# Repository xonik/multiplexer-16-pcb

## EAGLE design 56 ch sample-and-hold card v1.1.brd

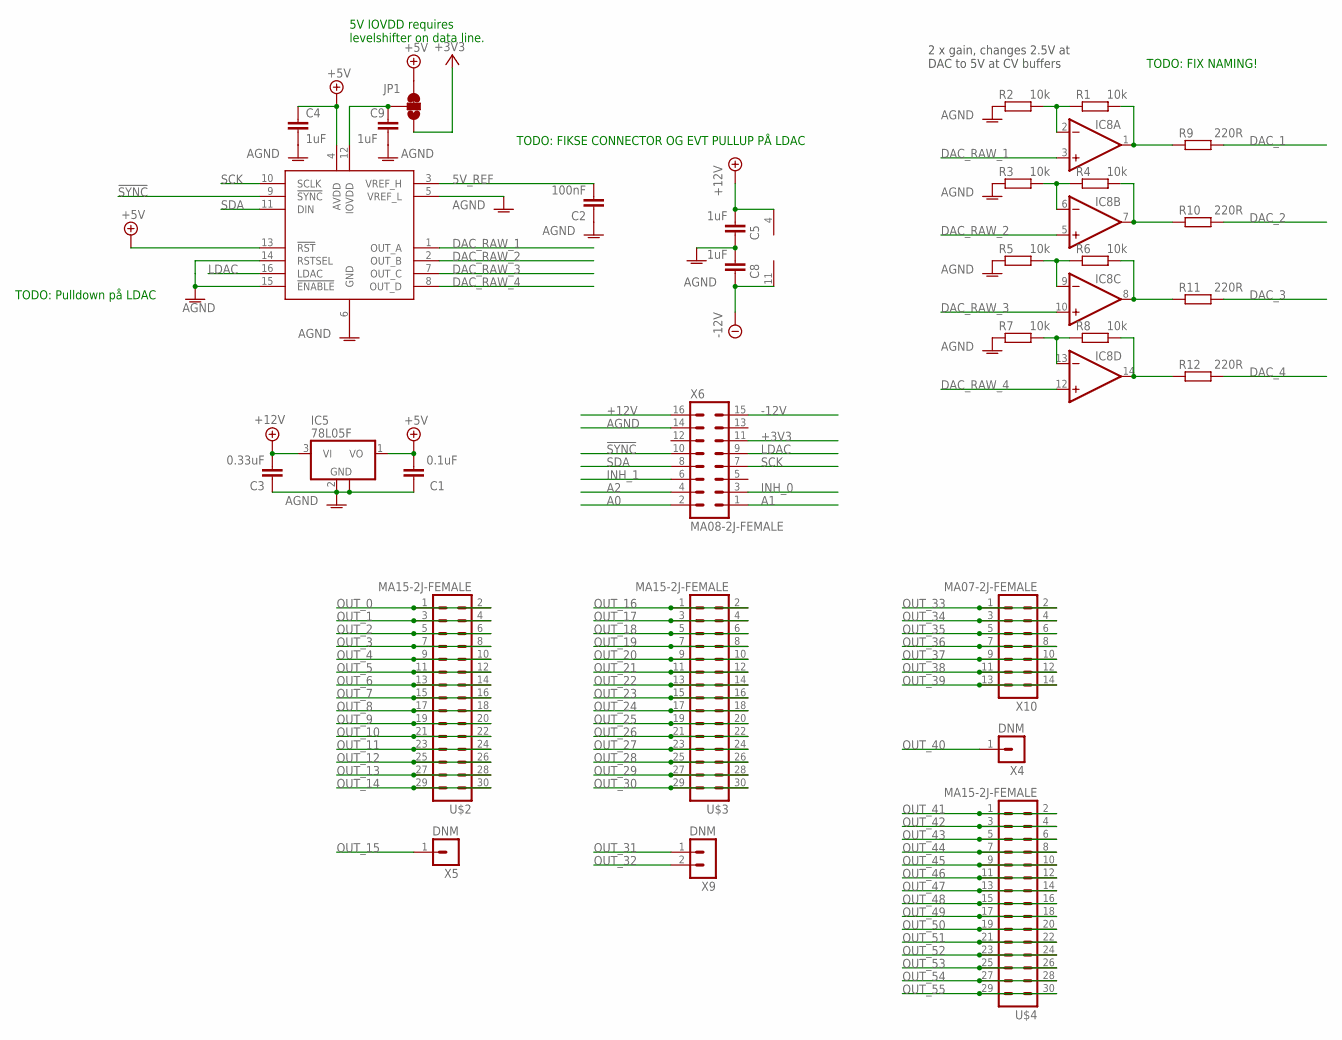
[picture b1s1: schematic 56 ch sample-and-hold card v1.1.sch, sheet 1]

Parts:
C1: 0.1uF; C0603
C2: 100nF; C0603
C3: 0.33uF; C0603
C4, C5, C8, C9: 1uF; C0402-J
IC2: DAC8565F; DIL16-FM-CON
IC5: 78L05F; SOT89
IC8: TL074JT; TSSOP14J
JP1: JUMPER-SMT_3_1-NC_TRACE_NO-SILK_DNM; SMT-JUMPER_3_1-NC_TRACE_NO-SILK
R1, R2, R3, R4, R5, R6, R7, R8: 10k; R0603
R9, R10, R11, R12: 220R; R0603
U$2, U$3, U$4: MA15-2J-FEMALE; MA15-2J
X4, X5: DNM; MA01N-1J
X6: MA08-2J-FEMALE; MA08-2J
X9: DNM; MA02N-1J
X10: MA07-2J-FEMALE; MA07-2J

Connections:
5V_REF: C2.2, IC2.3 (VREF_H)
!SYNC: IC2.9 (!SYNC), X6.10
+3V3: JP1.1, X6.11
+5V: C1.2, C4.1, IC2.4 (AVDD), IC2.13 (!RST), IC5.1 (VO), JP1.3; also elsewhere on the board
+12V: C3.2, C5.1, IC5.3 (VI), IC8.4 (V+), X6.16; also elsewhere on the board
-12V: C8.2, IC8.11 (V-), X6.15; also elsewhere on the board
A0: X6.2; also elsewhere on the board
A1: X6.1; also elsewhere on the board
A2: X6.4; also elsewhere on the board
AGND: C1.1, C2.1, C3.1, C4.2, C5.2, C8.1, C9.2, IC2.5 (VREF_L), IC2.6 (GND), IC2.14 (RSTSEL), IC2.15 (!ENABLE), IC5.2 (GND), IC5.2@1 (GND), R2.1, R3.1, R5.1, R7.1, X6.14; also elsewhere on the board
DAC_1: R9.2; also elsewhere on the board
DAC_2: R10.2; also elsewhere on the board
DAC_3: R11.2; also elsewhere on the board
DAC_4: R12.2; also elsewhere on the board
DAC_BUF_1: IC8.1 (OUT), R1.2, R9.1
DAC_BUF_2: IC8.7 (OUT), R4.2, R10.1
DAC_BUF_3: IC8.8 (OUT), R6.2, R11.1
DAC_BUF_4: IC8.14 (OUT), R8.2, R12.1
DAC_RAW_1: IC2.1 (OUT_A), IC8.3 (+IN)
DAC_RAW_2: IC2.2 (OUT_B), IC8.5 (+IN)
DAC_RAW_3: IC2.7 (OUT_C), IC8.10 (+IN)
DAC_RAW_4: IC2.8 (OUT_D), IC8.12 (+IN)
INH_0: X6.3; also elsewhere on the board
INH_1: X6.6; also elsewhere on the board
LDAC: IC2.16 (LDAC), X6.9
unnamed: C9.1, IC2.12 (IOVDD), JP1.2
unnamed: IC8.2 (-IN), R1.1, R2.2
unnamed: IC8.6 (-IN), R3.2, R4.1
unnamed: IC8.9 (-IN), R5.2, R6.1
unnamed: IC8.13 (-IN), R7.2, R8.1
OUT_0: U$2.1, U$2.2; also elsewhere on the board
OUT_1: U$2.3, U$2.4; also elsewhere on the board
OUT_2: U$2.5, U$2.6; also elsewhere on the board
OUT_3: U$2.7, U$2.8; also elsewhere on the board
OUT_4: U$2.9, U$2.10; also elsewhere on the board
OUT_5: U$2.11, U$2.12; also elsewhere on the board
OUT_6: U$2.13, U$2.14; also elsewhere on the board
OUT_7: U$2.15, U$2.16; also elsewhere on the board
OUT_8: U$2.17, U$2.18; also elsewhere on the board
OUT_9: U$2.19, U$2.20; also elsewhere on the board
OUT_10: U$2.21, U$2.22; also elsewhere on the board
OUT_11: U$2.23, U$2.24; also elsewhere on the board
OUT_12: U$2.25, U$2.26; also elsewhere on the board
OUT_13: U$2.27, U$2.28; also elsewhere on the board
OUT_14: U$2.29, U$2.30; also elsewhere on the board
OUT_15: X5.1; also elsewhere on the board
OUT_16: U$3.1, U$3.2; also elsewhere on the board
OUT_17: U$3.3, U$3.4; also elsewhere on the board
OUT_18: U$3.5, U$3.6; also elsewhere on the board
OUT_19: U$3.7, U$3.8; also elsewhere on the board
OUT_20: U$3.9, U$3.10; also elsewhere on the board
OUT_21: U$3.11, U$3.12; also elsewhere on the board
OUT_22: U$3.13, U$3.14; also elsewhere on the board
OUT_23: U$3.15, U$3.16; also elsewhere on the board
OUT_24: U$3.17, U$3.18; also elsewhere on the board
OUT_25: U$3.19, U$3.20; also elsewhere on the board
OUT_26: U$3.21, U$3.22; also elsewhere on the board
OUT_27: U$3.23, U$3.24; also elsewhere on the board
OUT_28: U$3.25, U$3.26; also elsewhere on the board
OUT_29: U$3.27, U$3.28; also elsewhere on the board
OUT_30: U$3.29, U$3.30; also elsewhere on the board
OUT_31: X9.1; also elsewhere on the board
OUT_32: X9.2; also elsewhere on the board
OUT_33: X10.1, X10.2; also elsewhere on the board
OUT_34: X10.3, X10.4; also elsewhere on the board
OUT_35: X10.5, X10.6; also elsewhere on the board
OUT_36: X10.7, X10.8; also elsewhere on the board
OUT_37: X10.9, X10.10; also elsewhere on the board
OUT_38: X10.11, X10.12; also elsewhere on the board
OUT_39: X10.13, X10.14; also elsewhere on the board
OUT_40: X4.1; also elsewhere on the board
OUT_41: U$4.1, U$4.2; also elsewhere on the board
OUT_42: U$4.3, U$4.4; also elsewhere on the board
OUT_43: U$4.5, U$4.6; also elsewhere on the board
OUT_44: U$4.7, U$4.8; also elsewhere on the board
OUT_45: U$4.9, U$4.10; also elsewhere on the board
OUT_46: U$4.11, U$4.12; also elsewhere on the board
OUT_47: U$4.13, U$4.14; also elsewhere on the board
OUT_48: U$4.15, U$4.16; also elsewhere on the board
OUT_49: U$4.17, U$4.18; also elsewhere on the board
OUT_50: U$4.19, U$4.20; also elsewhere on the board
OUT_51: U$4.21, U$4.22; also elsewhere on the board
OUT_52: U$4.23, U$4.24; also elsewhere on the board
OUT_53: U$4.25, U$4.26; also elsewhere on the board
OUT_54: U$4.27, U$4.28; also elsewhere on the board
OUT_55: U$4.29, U$4.30; also elsewhere on the board
SCK: IC2.10 (SCLK), X6.7
SDA: IC2.11 (DIN), X6.8

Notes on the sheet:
5V IOVDD requires levelshifter on data line.
TODO: FIKSE CONNECTOR OG EVT PULLUP PÅ LDAC
TODO: Pulldown på LDAC
TODO: FIX NAMING!
2 x gain, changes 2.5V at DAC to 5V at CV buffers

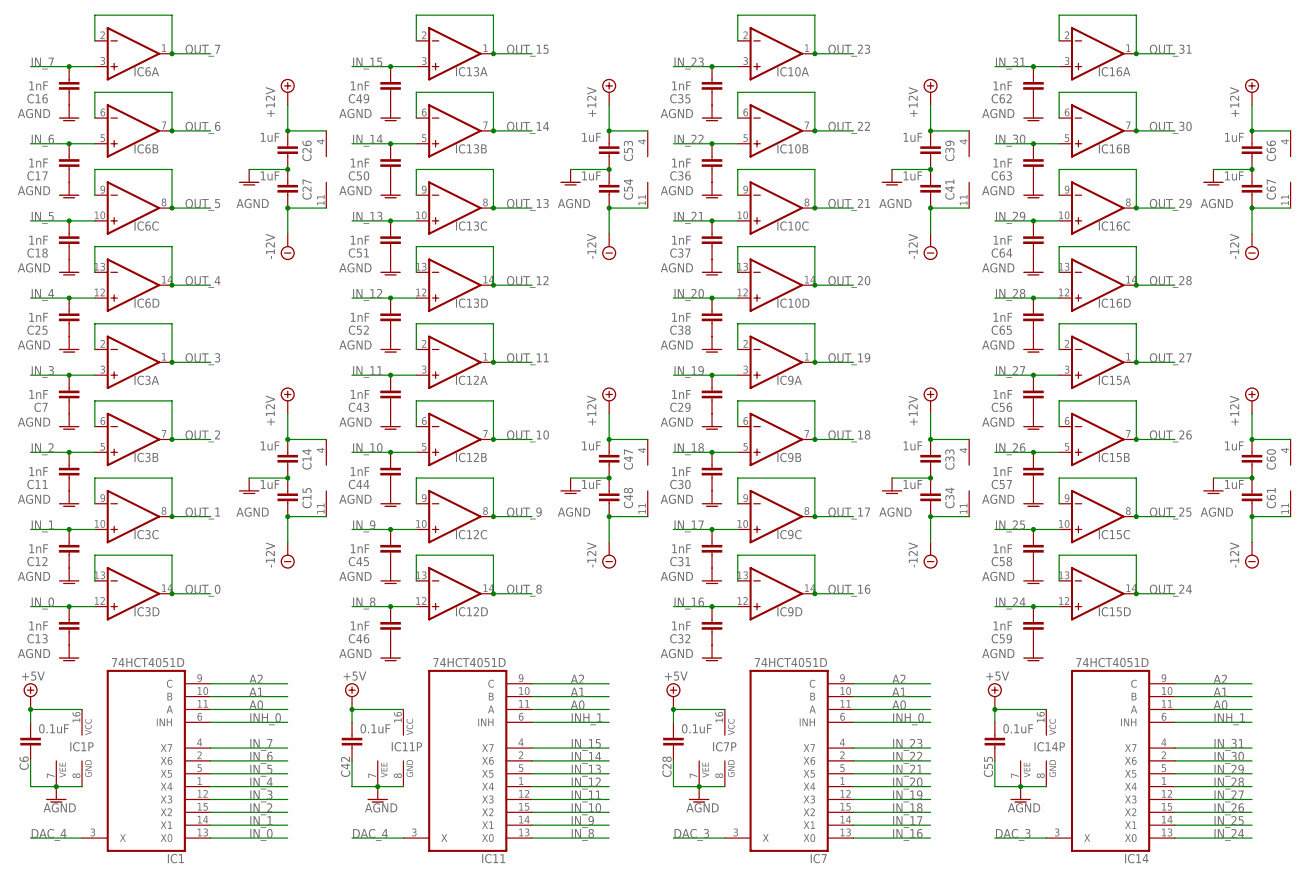
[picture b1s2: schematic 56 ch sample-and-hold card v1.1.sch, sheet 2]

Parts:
C6, C28, C42, C55: 0.1uF; C0402-J
C7, C11, C12, C13, C16, C17, C18, C25, C29, C30, C31, C32, C35, C36, C37, C38, C43, C44, C45, C46, C49, C50, C51, C52, C56, C57, C58, C59, C62, C63, C64, C65: 1nF; C0603-J
C14, C15, C26, C27, C33, C34, C39, C41, C47, C48, C53, C54, C60, C61, C66, C67: 1uF; C0402-J
IC1, IC7, IC11, IC14: 74HCT4051D; SO16
IC3, IC6, IC9, IC10, IC12, IC13, IC15, IC16: TL074JT; TSSOP14J

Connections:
+5V: C6.2, C28.2, C42.2, C55.2, IC1.16 (VCC), IC7.16 (VCC), IC11.16 (VCC), IC14.16 (VCC); also elsewhere on the board
+12V: C14.1, C26.1, C33.1, C39.1, C47.1, C53.1, C60.1, C66.1, IC3.4 (V+), IC6.4 (V+), IC9.4 (V+), IC10.4 (V+), IC12.4 (V+), IC13.4 (V+), IC15.4 (V+), IC16.4 (V+); also elsewhere on the board
-12V: C15.2, C27.2, C34.2, C41.2, C48.2, C54.2, C61.2, C67.2, IC3.11 (V-), IC6.11 (V-), IC9.11 (V-), IC10.11 (V-), IC12.11 (V-), IC13.11 (V-), IC15.11 (V-), IC16.11 (V-); also elsewhere on the board
A0: IC1.11 (A), IC7.11 (A), IC11.11 (A), IC14.11 (A); also elsewhere on the board
A1: IC1.10 (B), IC7.10 (B), IC11.10 (B), IC14.10 (B); also elsewhere on the board
A2: IC1.9 (C), IC7.9 (C), IC11.9 (C), IC14.9 (C); also elsewhere on the board
AGND: C6.1, C7.1, C11.1, C12.1, C13.1, C14.2, C15.1, C16.1, C17.1, C18.1, C25.1, C26.2, C27.1, C28.1, C29.1, C30.1, C31.1, C32.1, C33.2, C34.1, C35.1, C36.1, C37.1, C38.1, C39.2, C41.1, C42.1, C43.1, C44.1, C45.1, C46.1, C47.2, C48.1, C49.1, C50.1, C51.1, C52.1, C53.2, C54.1, C55.1, C56.1, C57.1, C58.1, C59.1, C60.2, C61.1, C62.1, C63.1, C64.1, C65.1, C66.2, C67.1, IC1.7 (VEE), IC1.8 (GND), IC7.7 (VEE), IC7.8 (GND), IC11.7 (VEE), IC11.8 (GND), IC14.7 (VEE), IC14.8 (GND); also elsewhere on the board
DAC_3: IC7.3 (X), IC14.3 (X); also elsewhere on the board
DAC_4: IC1.3 (X), IC11.3 (X); also elsewhere on the board
INH_0: IC1.6 (INH), IC7.6 (INH); also elsewhere on the board
INH_1: IC11.6 (INH), IC14.6 (INH); also elsewhere on the board
IN_0: C13.2, IC1.13 (X0), IC3.12 (+IN)
IN_1: C12.2, IC1.14 (X1), IC3.10 (+IN)
IN_2: C11.2, IC1.15 (X2), IC3.5 (+IN)
IN_3: C7.2, IC1.12 (X3), IC3.3 (+IN)
IN_4: C25.2, IC1.1 (X4), IC6.12 (+IN)
IN_5: C18.2, IC1.5 (X5), IC6.10 (+IN)
IN_6: C17.2, IC1.2 (X6), IC6.5 (+IN)
IN_7: C16.2, IC1.4 (X7), IC6.3 (+IN)
IN_8: C46.2, IC11.13 (X0), IC12.12 (+IN)
IN_9: C45.2, IC11.14 (X1), IC12.10 (+IN)
IN_10: C44.2, IC11.15 (X2), IC12.5 (+IN)
IN_11: C43.2, IC11.12 (X3), IC12.3 (+IN)
IN_12: C52.2, IC11.1 (X4), IC13.12 (+IN)
IN_13: C51.2, IC11.5 (X5), IC13.10 (+IN)
IN_14: C50.2, IC11.2 (X6), IC13.5 (+IN)
IN_15: C49.2, IC11.4 (X7), IC13.3 (+IN)
IN_16: C32.2, IC7.13 (X0), IC9.12 (+IN)
IN_17: C31.2, IC7.14 (X1), IC9.10 (+IN)
IN_18: C30.2, IC7.15 (X2), IC9.5 (+IN)
IN_19: C29.2, IC7.12 (X3), IC9.3 (+IN)
IN_20: C38.2, IC7.1 (X4), IC10.12 (+IN)
IN_21: C37.2, IC7.5 (X5), IC10.10 (+IN)
IN_22: C36.2, IC7.2 (X6), IC10.5 (+IN)
IN_23: C35.2, IC7.4 (X7), IC10.3 (+IN)
IN_24: C59.2, IC14.13 (X0), IC15.12 (+IN)
IN_25: C58.2, IC14.14 (X1), IC15.10 (+IN)
IN_26: C57.2, IC14.15 (X2), IC15.5 (+IN)
IN_27: C56.2, IC14.12 (X3), IC15.3 (+IN)
IN_28: C65.2, IC14.1 (X4), IC16.12 (+IN)
IN_29: C64.2, IC14.5 (X5), IC16.10 (+IN)
IN_30: C63.2, IC14.2 (X6), IC16.5 (+IN)
IN_31: C62.2, IC14.4 (X7), IC16.3 (+IN)
OUT_0: IC3.13 (-IN), IC3.14 (OUT); also elsewhere on the board
OUT_1: IC3.8 (OUT), IC3.9 (-IN); also elsewhere on the board
OUT_2: IC3.6 (-IN), IC3.7 (OUT); also elsewhere on the board
OUT_3: IC3.1 (OUT), IC3.2 (-IN); also elsewhere on the board
OUT_4: IC6.13 (-IN), IC6.14 (OUT); also elsewhere on the board
OUT_5: IC6.8 (OUT), IC6.9 (-IN); also elsewhere on the board
OUT_6: IC6.6 (-IN), IC6.7 (OUT); also elsewhere on the board
OUT_7: IC6.1 (OUT), IC6.2 (-IN); also elsewhere on the board
OUT_8: IC12.13 (-IN), IC12.14 (OUT); also elsewhere on the board
OUT_9: IC12.8 (OUT), IC12.9 (-IN); also elsewhere on the board
OUT_10: IC12.6 (-IN), IC12.7 (OUT); also elsewhere on the board
OUT_11: IC12.1 (OUT), IC12.2 (-IN); also elsewhere on the board
OUT_12: IC13.13 (-IN), IC13.14 (OUT); also elsewhere on the board
OUT_13: IC13.8 (OUT), IC13.9 (-IN); also elsewhere on the board
OUT_14: IC13.6 (-IN), IC13.7 (OUT); also elsewhere on the board
OUT_15: IC13.1 (OUT), IC13.2 (-IN); also elsewhere on the board
OUT_16: IC9.13 (-IN), IC9.14 (OUT); also elsewhere on the board
OUT_17: IC9.8 (OUT), IC9.9 (-IN); also elsewhere on the board
OUT_18: IC9.6 (-IN), IC9.7 (OUT); also elsewhere on the board
OUT_19: IC9.1 (OUT), IC9.2 (-IN); also elsewhere on the board
OUT_20: IC10.13 (-IN), IC10.14 (OUT); also elsewhere on the board
OUT_21: IC10.8 (OUT), IC10.9 (-IN); also elsewhere on the board
OUT_22: IC10.6 (-IN), IC10.7 (OUT); also elsewhere on the board
OUT_23: IC10.1 (OUT), IC10.2 (-IN); also elsewhere on the board
OUT_24: IC15.13 (-IN), IC15.14 (OUT); also elsewhere on the board
OUT_25: IC15.8 (OUT), IC15.9 (-IN); also elsewhere on the board
OUT_26: IC15.6 (-IN), IC15.7 (OUT); also elsewhere on the board
OUT_27: IC15.1 (OUT), IC15.2 (-IN); also elsewhere on the board
OUT_28: IC16.13 (-IN), IC16.14 (OUT); also elsewhere on the board
OUT_29: IC16.8 (OUT), IC16.9 (-IN); also elsewhere on the board
OUT_30: IC16.6 (-IN), IC16.7 (OUT); also elsewhere on the board
OUT_31: IC16.1 (OUT), IC16.2 (-IN); also elsewhere on the board

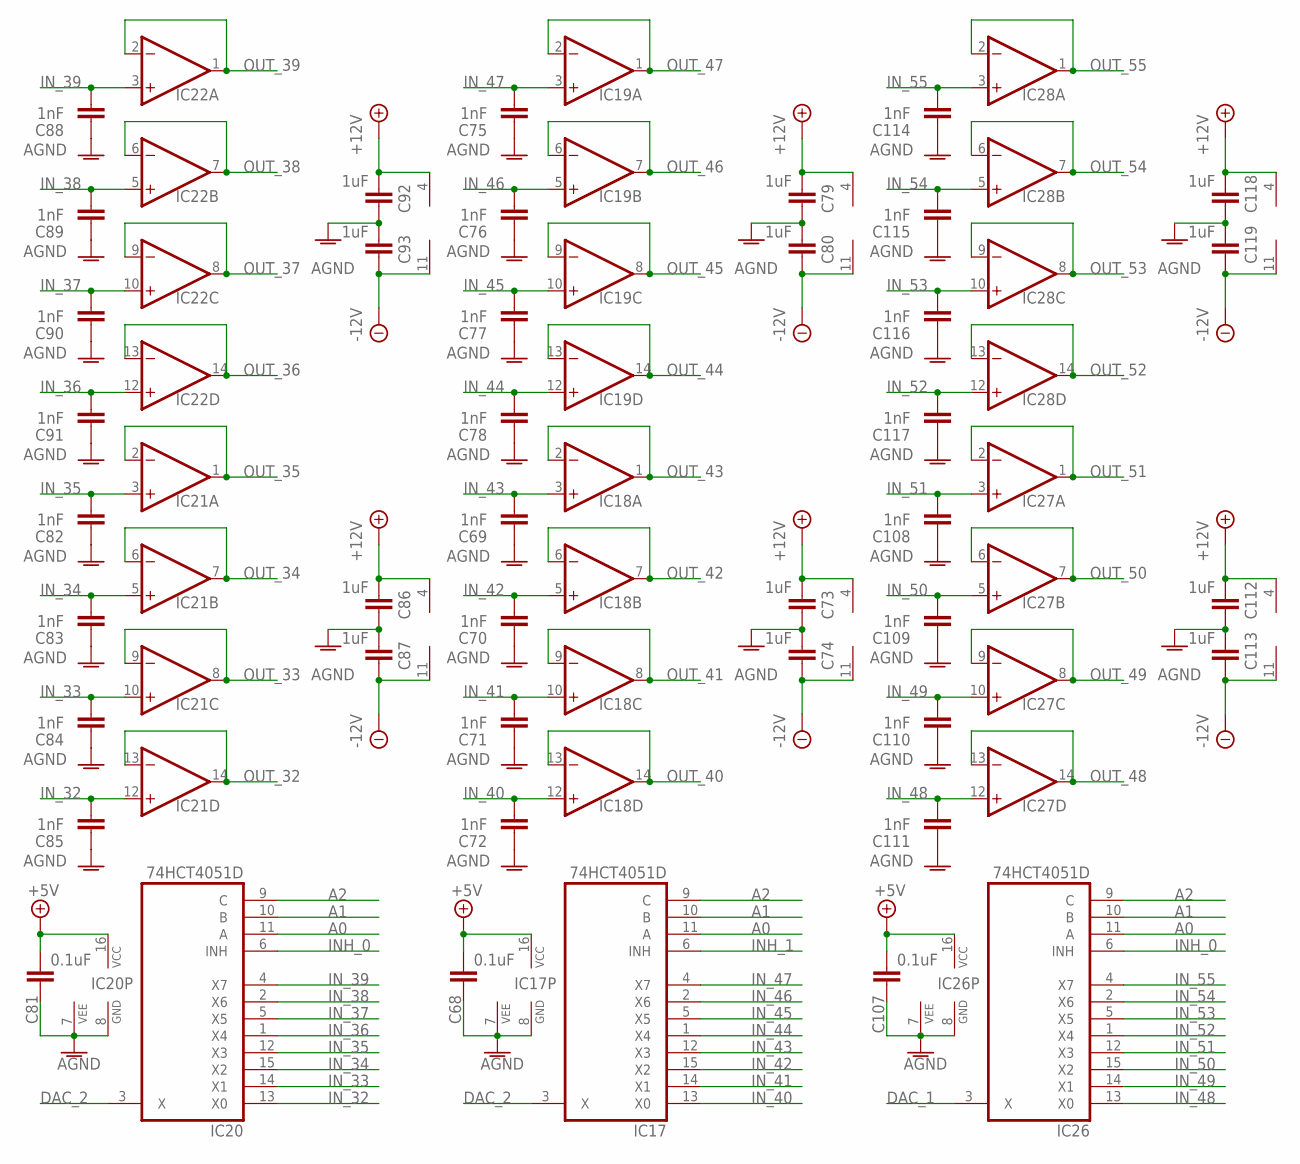
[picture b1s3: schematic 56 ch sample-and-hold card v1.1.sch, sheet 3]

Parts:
C68, C81, C107: 0.1uF; C0402-J
C69, C70, C71, C72, C75, C76, C77, C78, C82, C83, C84, C85, C88, C89, C90, C91, C108, C109, C110, C111, C114, C115, C116, C117: 1nF; C0603-J
C73, C74, C79, C80, C86, C87, C92, C93, C112, C113, C118, C119: 1uF; C0402-J
IC17, IC20, IC26: 74HCT4051D; SO16
IC18, IC19, IC21, IC22, IC27, IC28: TL074JT; TSSOP14J

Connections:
+5V: C68.2, C81.2, C107.2, IC17.16 (VCC), IC20.16 (VCC), IC26.16 (VCC); also elsewhere on the board
+12V: C73.1, C79.1, C86.1, C92.1, C112.1, C118.1, IC18.4 (V+), IC19.4 (V+), IC21.4 (V+), IC22.4 (V+), IC27.4 (V+), IC28.4 (V+); also elsewhere on the board
-12V: C74.2, C80.2, C87.2, C93.2, C113.2, C119.2, IC18.11 (V-), IC19.11 (V-), IC21.11 (V-), IC22.11 (V-), IC27.11 (V-), IC28.11 (V-); also elsewhere on the board
A0: IC17.11 (A), IC20.11 (A), IC26.11 (A); also elsewhere on the board
A1: IC17.10 (B), IC20.10 (B), IC26.10 (B); also elsewhere on the board
A2: IC17.9 (C), IC20.9 (C), IC26.9 (C); also elsewhere on the board
AGND: C68.1, C69.1, C70.1, C71.1, C72.1, C73.2, C74.1, C75.1, C76.1, C77.1, C78.1, C79.2, C80.1, C81.1, C82.1, C83.1, C84.1, C85.1, C86.2, C87.1, C88.1, C89.1, C90.1, C91.1, C92.2, C93.1, C107.1, C108.1, C109.1, C110.1, C111.1, C112.2, C113.1, C114.1, C115.1, C116.1, C117.1, C118.2, C119.1, IC17.7 (VEE), IC17.8 (GND), IC20.7 (VEE), IC20.8 (GND), IC26.7 (VEE), IC26.8 (GND); also elsewhere on the board
DAC_1: IC26.3 (X); also elsewhere on the board
DAC_2: IC17.3 (X), IC20.3 (X); also elsewhere on the board
INH_0: IC20.6 (INH), IC26.6 (INH); also elsewhere on the board
INH_1: IC17.6 (INH); also elsewhere on the board
IN_32: C85.2, IC20.13 (X0), IC21.12 (+IN)
IN_33: C84.2, IC20.14 (X1), IC21.10 (+IN)
IN_34: C83.2, IC20.15 (X2), IC21.5 (+IN)
IN_35: C82.2, IC20.12 (X3), IC21.3 (+IN)
IN_36: C91.2, IC20.1 (X4), IC22.12 (+IN)
IN_37: C90.2, IC20.5 (X5), IC22.10 (+IN)
IN_38: C89.2, IC20.2 (X6), IC22.5 (+IN)
IN_39: C88.2, IC20.4 (X7), IC22.3 (+IN)
IN_40: C72.2, IC17.13 (X0), IC18.12 (+IN)
IN_41: C71.2, IC17.14 (X1), IC18.10 (+IN)
IN_42: C70.2, IC17.15 (X2), IC18.5 (+IN)
IN_43: C69.2, IC17.12 (X3), IC18.3 (+IN)
IN_44: C78.2, IC17.1 (X4), IC19.12 (+IN)
IN_45: C77.2, IC17.5 (X5), IC19.10 (+IN)
IN_46: C76.2, IC17.2 (X6), IC19.5 (+IN)
IN_47: C75.2, IC17.4 (X7), IC19.3 (+IN)
IN_48: C111.2, IC26.13 (X0), IC27.12 (+IN)
IN_49: C110.2, IC26.14 (X1), IC27.10 (+IN)
IN_50: C109.2, IC26.15 (X2), IC27.5 (+IN)
IN_51: C108.2, IC26.12 (X3), IC27.3 (+IN)
IN_52: C117.2, IC26.1 (X4), IC28.12 (+IN)
IN_53: C116.2, IC26.5 (X5), IC28.10 (+IN)
IN_54: C115.2, IC26.2 (X6), IC28.5 (+IN)
IN_55: C114.2, IC26.4 (X7), IC28.3 (+IN)
OUT_32: IC21.13 (-IN), IC21.14 (OUT); also elsewhere on the board
OUT_33: IC21.8 (OUT), IC21.9 (-IN); also elsewhere on the board
OUT_34: IC21.6 (-IN), IC21.7 (OUT); also elsewhere on the board
OUT_35: IC21.1 (OUT), IC21.2 (-IN); also elsewhere on the board
OUT_36: IC22.13 (-IN), IC22.14 (OUT); also elsewhere on the board
OUT_37: IC22.8 (OUT), IC22.9 (-IN); also elsewhere on the board
OUT_38: IC22.6 (-IN), IC22.7 (OUT); also elsewhere on the board
OUT_39: IC22.1 (OUT), IC22.2 (-IN); also elsewhere on the board
OUT_40: IC18.13 (-IN), IC18.14 (OUT); also elsewhere on the board
OUT_41: IC18.8 (OUT), IC18.9 (-IN); also elsewhere on the board
OUT_42: IC18.6 (-IN), IC18.7 (OUT); also elsewhere on the board
OUT_43: IC18.1 (OUT), IC18.2 (-IN); also elsewhere on the board
OUT_44: IC19.13 (-IN), IC19.14 (OUT); also elsewhere on the board
OUT_45: IC19.8 (OUT), IC19.9 (-IN); also elsewhere on the board
OUT_46: IC19.6 (-IN), IC19.7 (OUT); also elsewhere on the board
OUT_47: IC19.1 (OUT), IC19.2 (-IN); also elsewhere on the board
OUT_48: IC27.13 (-IN), IC27.14 (OUT); also elsewhere on the board
OUT_49: IC27.8 (OUT), IC27.9 (-IN); also elsewhere on the board
OUT_50: IC27.6 (-IN), IC27.7 (OUT); also elsewhere on the board
OUT_51: IC27.1 (OUT), IC27.2 (-IN); also elsewhere on the board
OUT_52: IC28.13 (-IN), IC28.14 (OUT); also elsewhere on the board
OUT_53: IC28.8 (OUT), IC28.9 (-IN); also elsewhere on the board
OUT_54: IC28.6 (-IN), IC28.7 (OUT); also elsewhere on the board
OUT_55: IC28.1 (OUT), IC28.2 (-IN); also elsewhere on the board

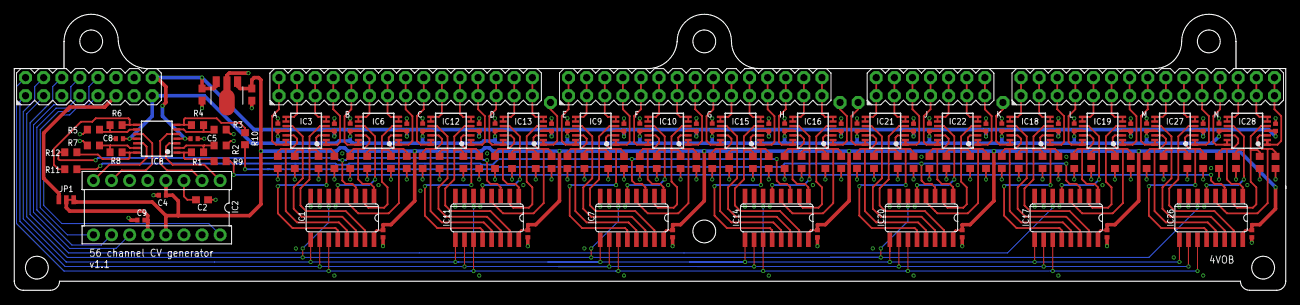
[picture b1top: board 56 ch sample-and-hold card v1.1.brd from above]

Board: 4 copper layers, 178.4 x 38.7 mm, 144 parts (1 on the bottom side), 144 nets.

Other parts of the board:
U$1: XONIK_LOGO_60

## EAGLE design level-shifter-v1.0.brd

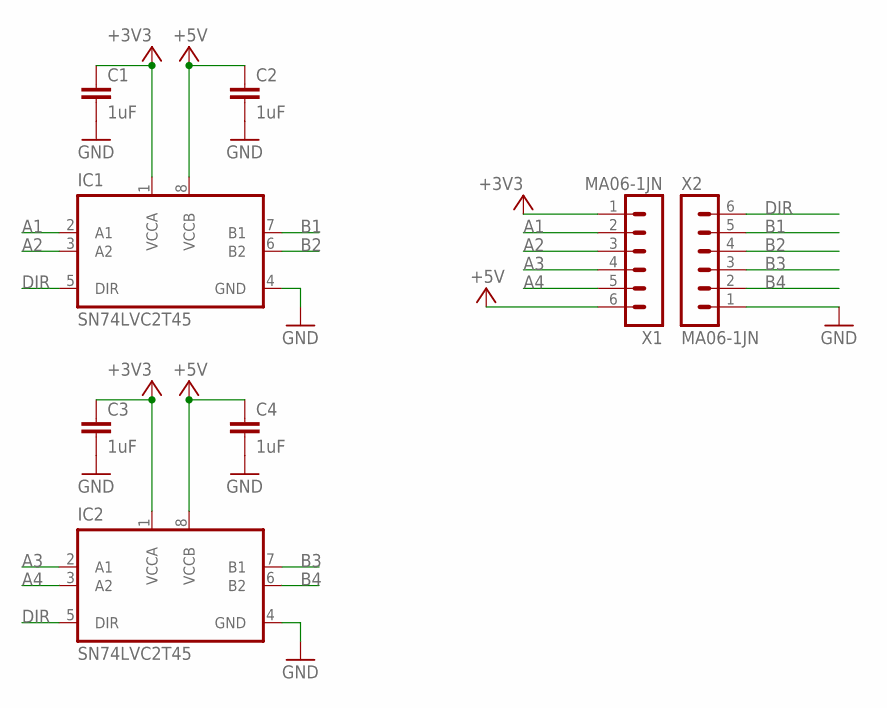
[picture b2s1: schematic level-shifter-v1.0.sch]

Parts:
C1, C2, C3, C4: 1uF; C0402-J
IC1, IC2: SN74LVC2T45; VSSOP8J
X1, X2: MA06-1JN; MA06N-1J

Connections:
+3V3: C1.1, C3.1, IC1.1 (VCCA), IC2.1 (VCCA), X1.1
+5V: C2.1, C4.1, IC1.8 (VCCB), IC2.8 (VCCB), X1.6
A1: IC1.2 (A1), X1.2
A2: IC1.3 (A2), X1.3
A3: IC2.2 (A1), X1.4
A4: IC2.3 (A2), X1.5
B1: IC1.7 (B1), X2.5
B2: IC1.6 (B2), X2.4
B3: IC2.7 (B1), X2.3
B4: IC2.6 (B2), X2.2
DIR: IC1.5 (DIR), IC2.5 (DIR), X2.6
GND: C1.2, C2.2, C3.2, C4.2, IC1.4 (GND), IC2.4 (GND), X2.1

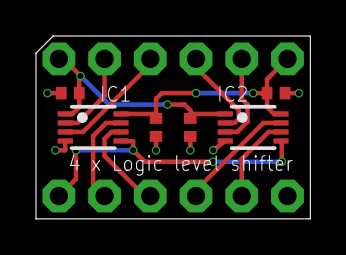
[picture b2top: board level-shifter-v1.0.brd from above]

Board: 2 copper layers, 15.2 x 10.2 mm, 8 parts (0 on the bottom side), 12 nets.

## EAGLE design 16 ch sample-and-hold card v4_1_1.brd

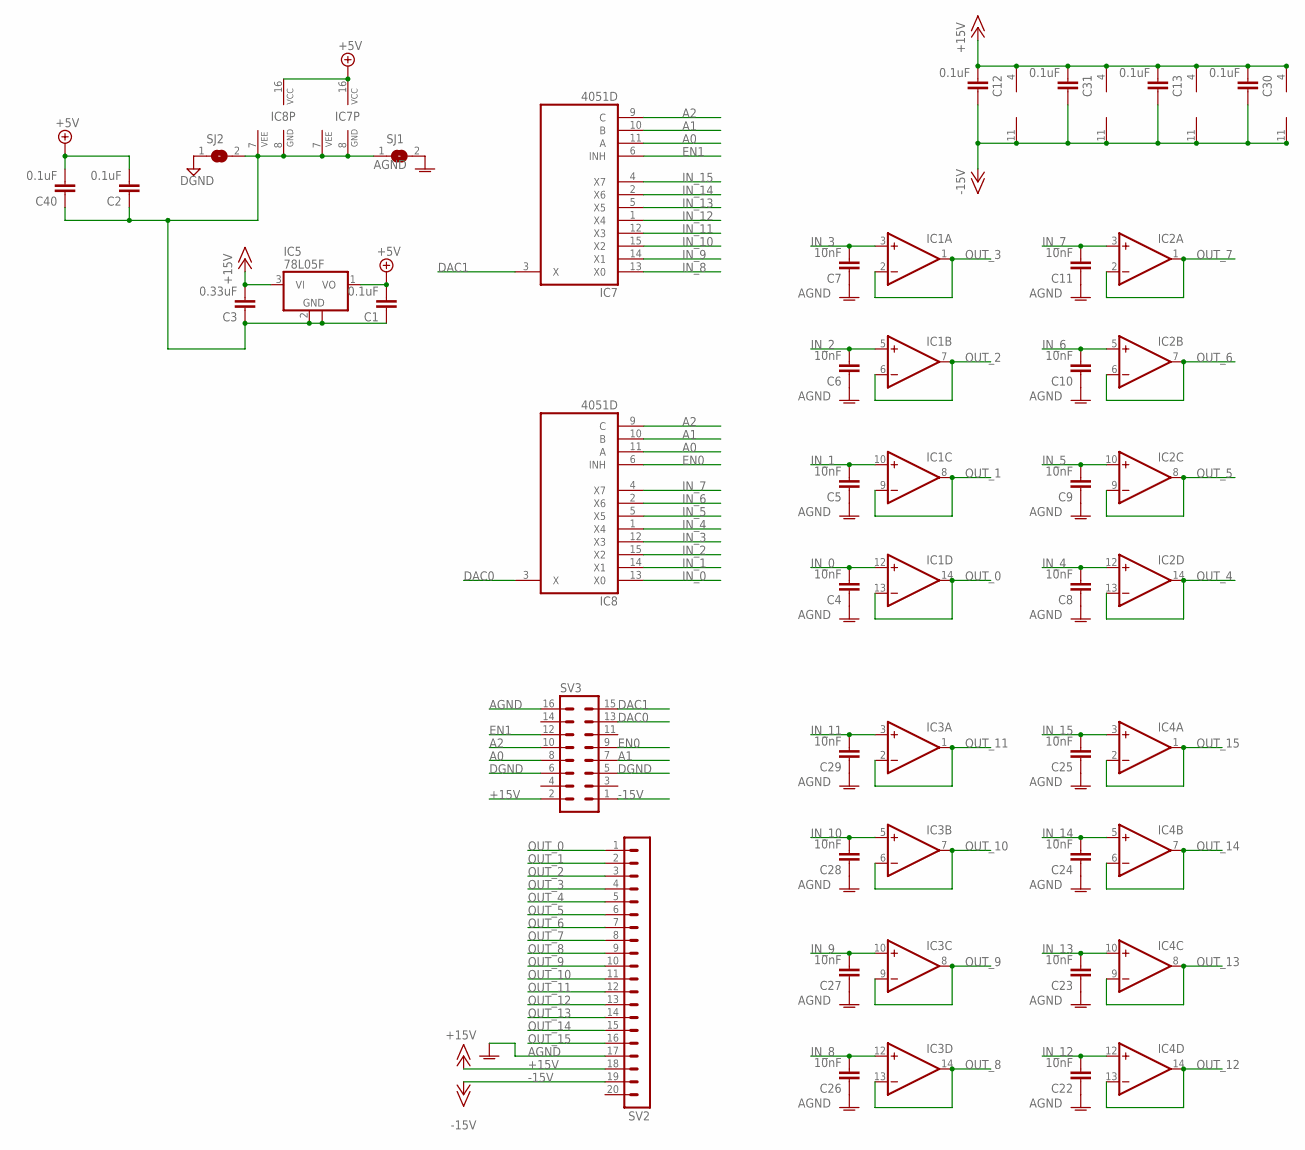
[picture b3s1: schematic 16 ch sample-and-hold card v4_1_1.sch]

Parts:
C1, C2, C12, C13, C30, C31, C40: 0.1uF; C0603
C3: 0.33uF; C0603
C4, C5, C6, C7, C8, C9, C10, C11, C22, C23, C24, C25, C26, C27, C28, C29: 10nF; C0805
IC1, IC2, IC3, IC4: TL074D; SO14
IC5: 78L05F; SOT89
IC7, IC8: 4051D; SO16
SJ1, SJ2: SJ
SV2: MA20-1
SV3: MA08-2J

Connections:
+5V: C1.2, C2.2, C40.2, IC5.1 (VO), IC7.16 (VCC), IC8.16 (VCC)
+15V: C3.2, C12.1, C13.1, C30.1, C31.1, IC1.4 (V+), IC2.4 (V+), IC3.4 (V+), IC4.4 (V+), IC5.3 (VI), SV2.18, SV3.2
-15V: C12.2, C13.2, C30.2, C31.2, IC1.11 (V-), IC2.11 (V-), IC3.11 (V-), IC4.11 (V-), SV2.19, SV3.1
A0: IC7.11 (A), IC8.11 (A), SV3.8
A1: IC7.10 (B), IC8.10 (B), SV3.7
A2: IC7.9 (C), IC8.9 (C), SV3.10
AGND: C4.1, C5.1, C6.1, C7.1, C8.1, C9.1, C10.1, C11.1, C22.1, C23.1, C24.1, C25.1, C26.1, C27.1, C28.1, C29.1, SJ1.2, SV2.17, SV3.16
DAC0: IC8.3 (X), SV3.13
DAC1: IC7.3 (X), SV3.15
DGND: SJ2.1, SV3.5, SV3.6
EN0: IC8.6 (INH), SV3.9
EN1: IC7.6 (INH), SV3.12
IN_0: C4.2, IC1.12 (+IN), IC8.13 (X0)
IN_1: C5.2, IC1.10 (+IN), IC8.14 (X1)
IN_2: C6.2, IC1.5 (+IN), IC8.15 (X2)
IN_3: C7.2, IC1.3 (+IN), IC8.12 (X3)
IN_4: C8.2, IC2.12 (+IN), IC8.1 (X4)
IN_5: C9.2, IC2.10 (+IN), IC8.5 (X5)
IN_6: C10.2, IC2.5 (+IN), IC8.2 (X6)
IN_7: C11.2, IC2.3 (+IN), IC8.4 (X7)
IN_8: C26.2, IC3.12 (+IN), IC7.13 (X0)
IN_9: C27.2, IC3.10 (+IN), IC7.14 (X1)
IN_10: C28.2, IC3.5 (+IN), IC7.15 (X2)
IN_11: C29.2, IC3.3 (+IN), IC7.12 (X3)
IN_12: C22.2, IC4.12 (+IN), IC7.1 (X4)
IN_13: C23.2, IC4.10 (+IN), IC7.5 (X5)
IN_14: C24.2, IC4.5 (+IN), IC7.2 (X6)
IN_15: C25.2, IC4.3 (+IN), IC7.4 (X7)
unnamed: C1.1, C2.1, C3.1, C40.1, IC5.2 (GND), IC5.2@1 (GND), IC7.7 (VEE), IC7.8 (GND), IC8.7 (VEE), IC8.8 (GND), SJ1.1, SJ2.2
OUT_0: IC1.13 (-IN), IC1.14 (OUT), SV2.1
OUT_1: IC1.8 (OUT), IC1.9 (-IN), SV2.2
OUT_2: IC1.6 (-IN), IC1.7 (OUT), SV2.3
OUT_3: IC1.1 (OUT), IC1.2 (-IN), SV2.4
OUT_4: IC2.13 (-IN), IC2.14 (OUT), SV2.5
OUT_5: IC2.8 (OUT), IC2.9 (-IN), SV2.6
OUT_6: IC2.6 (-IN), IC2.7 (OUT), SV2.7
OUT_7: IC2.1 (OUT), IC2.2 (-IN), SV2.8
OUT_8: IC3.13 (-IN), IC3.14 (OUT), SV2.9
OUT_9: IC3.8 (OUT), IC3.9 (-IN), SV2.10
OUT_10: IC3.6 (-IN), IC3.7 (OUT), SV2.11
OUT_11: IC3.1 (OUT), IC3.2 (-IN), SV2.12
OUT_12: IC4.13 (-IN), IC4.14 (OUT), SV2.13
OUT_13: IC4.8 (OUT), IC4.9 (-IN), SV2.14
OUT_14: IC4.6 (-IN), IC4.7 (OUT), SV2.15
OUT_15: IC4.1 (OUT), IC4.2 (-IN), SV2.16

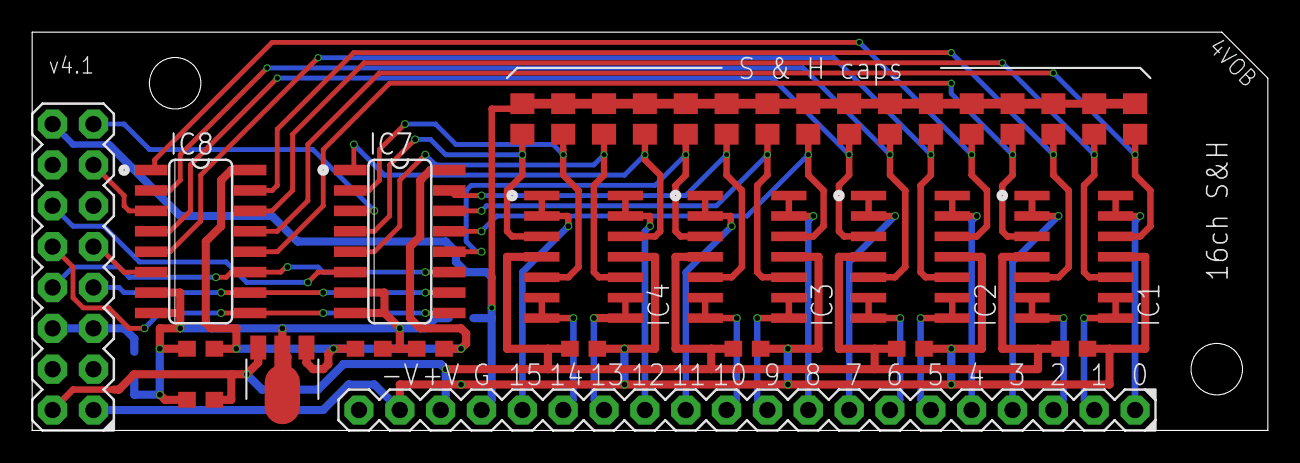
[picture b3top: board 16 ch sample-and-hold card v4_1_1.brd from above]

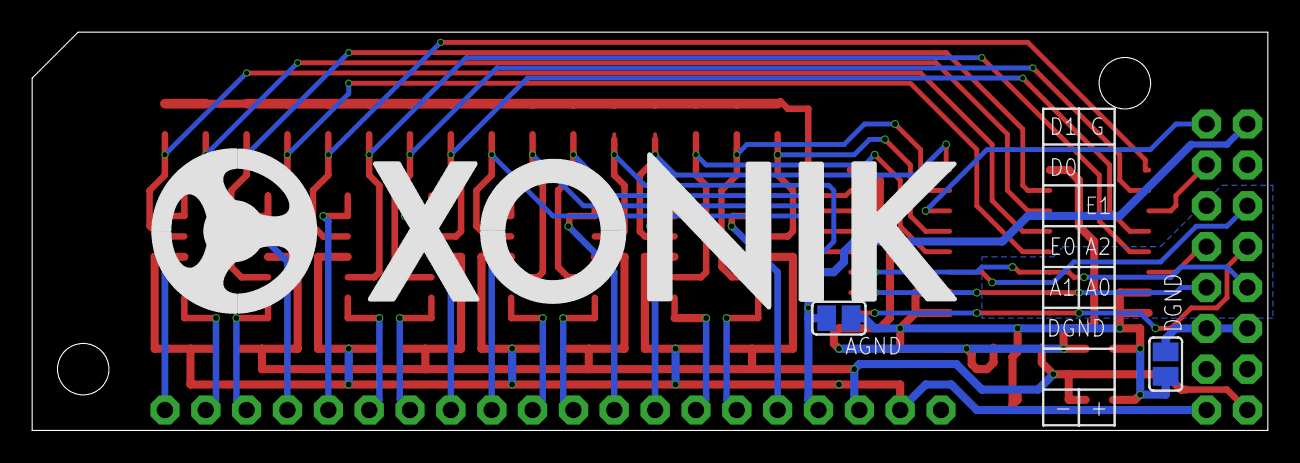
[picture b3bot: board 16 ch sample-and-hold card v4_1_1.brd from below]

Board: 2 copper layers, 76.8 x 24.8 mm, 36 parts (3 on the bottom side), 45 nets.

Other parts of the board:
U$1: XONIK_LOGO_50

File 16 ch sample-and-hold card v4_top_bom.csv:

Comment,Designator,Footprint,LCSC Part #
0.1uF,C1 C2 C12 C13 C30 C31 C40,C0603,
0.33uF,C3,C0603,
10nF,C4 C5 C6 C7 C8 C9 C10 C11 C22 C23 C24 C25 C26 C27 C28 C29,C1206,
78L05F,IC5,SOT89,
4051D,IC7 IC8,SO16,

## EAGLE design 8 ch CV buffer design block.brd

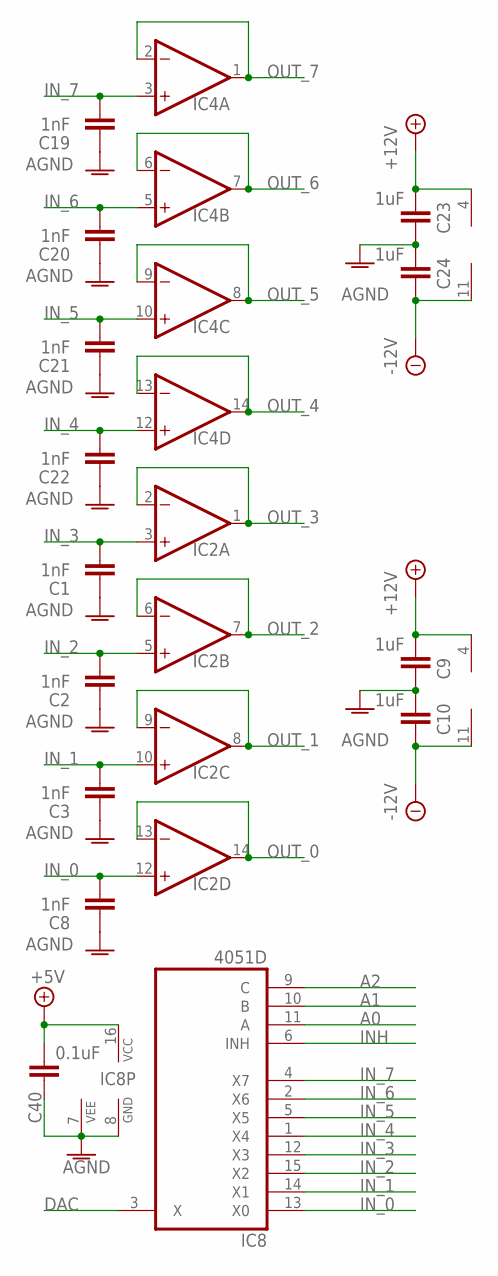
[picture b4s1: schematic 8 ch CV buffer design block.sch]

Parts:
C1, C2, C3, C8, C19, C20, C21, C22: 1nF; C0603-J
C9, C10, C23, C24: 1uF; C0402-J
C40: 0.1uF; C0402-J
IC2, IC4: TL074JT; TSSOP14J
IC8: 4051D; SO16

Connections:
+5V: C40.2, IC8.16 (VCC)
+12V: C9.1, C23.1, IC2.4 (V+), IC4.4 (V+)
-12V: C10.2, C24.2, IC2.11 (V-), IC4.11 (V-)
A0: IC8.11 (A)
A1: IC8.10 (B)
A2: IC8.9 (C)
AGND: C1.1, C2.1, C3.1, C8.1, C9.2, C10.1, C19.1, C20.1, C21.1, C22.1, C23.2, C24.1, C40.1, IC8.7 (VEE), IC8.8 (GND)
DAC: IC8.3 (X)
INH: IC8.6 (INH)
IN_0: C8.2, IC2.12 (+IN), IC8.13 (X0)
IN_1: C3.2, IC2.10 (+IN), IC8.14 (X1)
IN_2: C2.2, IC2.5 (+IN), IC8.15 (X2)
IN_3: C1.2, IC2.3 (+IN), IC8.12 (X3)
IN_4: C22.2, IC4.12 (+IN), IC8.1 (X4)
IN_5: C21.2, IC4.10 (+IN), IC8.5 (X5)
IN_6: C20.2, IC4.5 (+IN), IC8.2 (X6)
IN_7: C19.2, IC4.3 (+IN), IC8.4 (X7)
OUT_0: IC2.13 (-IN), IC2.14 (OUT)
OUT_1: IC2.8 (OUT), IC2.9 (-IN)
OUT_2: IC2.6 (-IN), IC2.7 (OUT)
OUT_3: IC2.1 (OUT), IC2.2 (-IN)
OUT_4: IC4.13 (-IN), IC4.14 (OUT)
OUT_5: IC4.8 (OUT), IC4.9 (-IN)
OUT_6: IC4.6 (-IN), IC4.7 (OUT)
OUT_7: IC4.1 (OUT), IC4.2 (-IN)

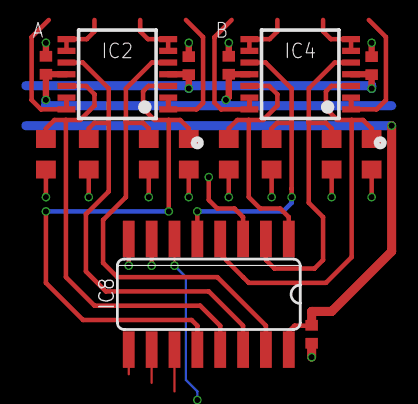
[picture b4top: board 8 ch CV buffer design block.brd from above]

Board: 2 copper layers, 16 parts (0 on the bottom side), 20 nets.

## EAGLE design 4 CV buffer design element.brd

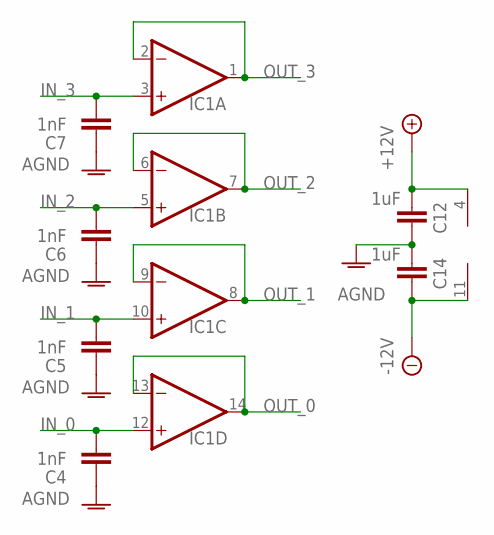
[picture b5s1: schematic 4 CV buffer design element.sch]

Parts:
C4, C5, C6, C7: 1nF; C0603-J
C12, C14: 1uF; C0402-J
IC1: TL074JT; TSSOP14J

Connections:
+12V: C12.1, IC1.4 (V+)
-12V: C14.2, IC1.11 (V-)
AGND: C4.1, C5.1, C6.1, C7.1, C12.2, C14.1
IN_0: C4.2, IC1.12 (+IN)
IN_1: C5.2, IC1.10 (+IN)
IN_2: C6.2, IC1.5 (+IN)
IN_3: C7.2, IC1.3 (+IN)
OUT_0: IC1.13 (-IN), IC1.14 (OUT)
OUT_1: IC1.8 (OUT), IC1.9 (-IN)
OUT_2: IC1.6 (-IN), IC1.7 (OUT)
OUT_3: IC1.1 (OUT), IC1.2 (-IN)

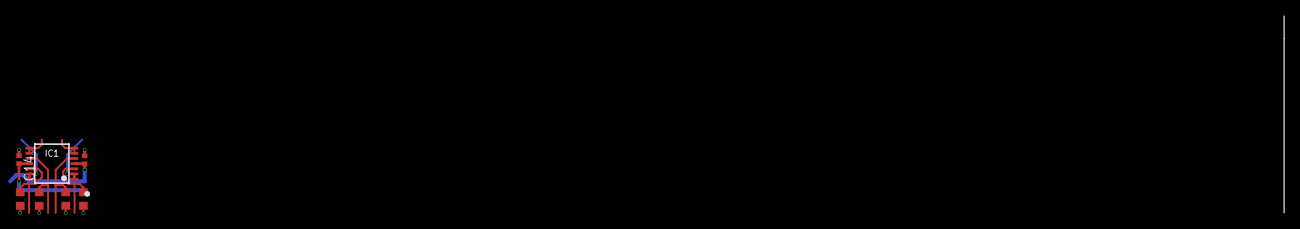
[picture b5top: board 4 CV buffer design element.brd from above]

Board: 2 copper layers, 7 parts (0 on the bottom side), 11 nets.

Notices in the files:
parts and their libraries:
SparkFun-Jumpers: Licensing: Creative Commons ShareAlike 4.0 International - https://creativecommons.org/licenses/by-sa/4.0
